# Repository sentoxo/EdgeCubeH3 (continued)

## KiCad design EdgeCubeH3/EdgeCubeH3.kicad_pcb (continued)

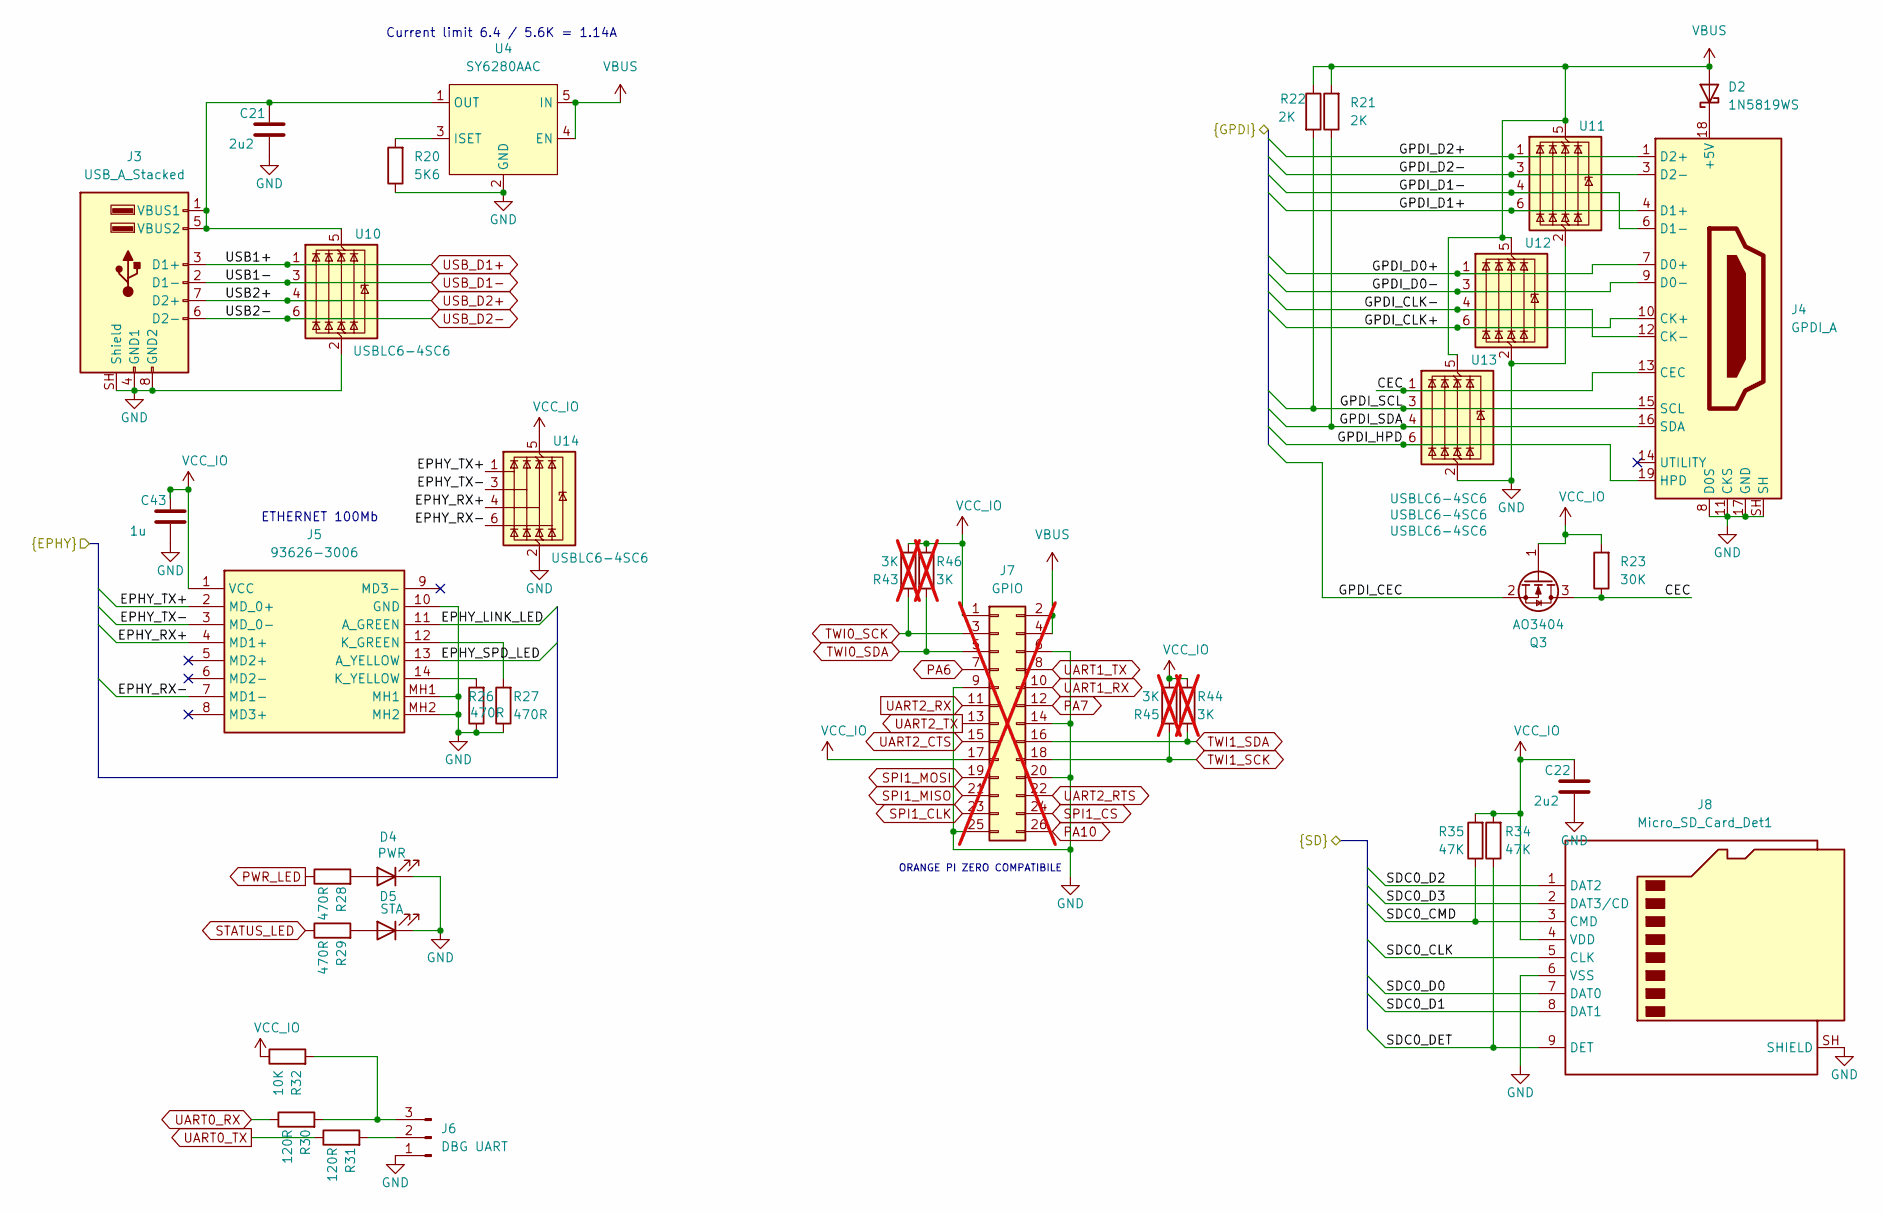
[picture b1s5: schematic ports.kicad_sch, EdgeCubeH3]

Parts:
C21, C22: 2u2; C_0603_1608Metric
C43: 1u; C_0603_1608Metric
D2: 1N5819WS; D_SOD-323
D4: PWR; LED_0805_2012Metric
D5: STA; LED_0805_2012Metric
J3: USB_A_Stacked; USB_A_CUI_UJ2-ADH-TH_Horizontal_Stacked
J4: GPDI_A; HDMI_A_Molex_208658-1001_Horizontal
J5: 93626-3006; 936263006; Mouser Part Number 538-93626-3006
J6: DBG UART; PinHeader_1x03_P2.54mm_Vertical
J7: GPIO; PinHeader_2x13_P2.54mm_Vertical; not fitted
J8: Micro_SD_Card_Det1; microSD_TF-01A
Q3: AO3404; SOT-23
R20: 5K6; R_0603_1608Metric
R21, R22: 2K; R_0603_1608Metric
R23: 30K; R_0603_1608Metric
R26, R27, R28, R29: 470R; R_0603_1608Metric
R30, R31: 120R; R_0603_1608Metric
R32: 10K; R_0603_1608Metric
R34, R35: 47K; R_0603_1608Metric
R43, R44, R45, R46: 3K; R_0603_1608Metric; not fitted
U4: SY6280AAC; SOT-23-5; LCSC Part # C55136
U10, U11, U12, U13, U14: USBLC6-4SC6; SOT-23-6

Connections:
/SoC/EPHY_LINK_LED: J5.11 (A_GREEN); also elsewhere on the board
/SoC/EPHY_RX+: J5.4 (MD1+), U14.4 (I/O3); also elsewhere on the board
/SoC/EPHY_RX-: J5.7 (MD1-), U14.6 (I/O4); also elsewhere on the board
/SoC/EPHY_SPD_LED: J5.13 (A_YELLOW); also elsewhere on the board
/SoC/EPHY_TX+: J5.2 (MD_0+), U14.1 (I/O1); also elsewhere on the board
/SoC/EPHY_TX-: J5.3 (MD_0-), U14.3 (I/O2); also elsewhere on the board
/SoC/GPDI_CEC: Q3.2 (S); also elsewhere on the board
/SoC/GPDI_CLK+: J4.10 (CK+), U12.6 (I/O4); also elsewhere on the board
/SoC/GPDI_CLK-: J4.12 (CK-), U12.4 (I/O3); also elsewhere on the board
/SoC/GPDI_D0+: J4.7 (D0+), U12.1 (I/O1); also elsewhere on the board
/SoC/GPDI_D0-: J4.9 (D0-), U12.3 (I/O2); also elsewhere on the board
/SoC/GPDI_D1+: J4.4 (D1+), U11.6 (I/O4); also elsewhere on the board
/SoC/GPDI_D1-: J4.6 (D1-), U11.4 (I/O3); also elsewhere on the board
/SoC/GPDI_D2+: J4.1 (D2+), U11.1 (I/O1); also elsewhere on the board
/SoC/GPDI_D2-: J4.3 (D2-), U11.3 (I/O2); also elsewhere on the board
/SoC/GPDI_HPD: J4.19 (HPD), U13.6 (I/O4); also elsewhere on the board
/SoC/GPDI_SCL: J4.15 (SCL), R22.2, U13.3 (I/O2); also elsewhere on the board
/SoC/GPDI_SDA: J4.16 (SDA), R21.1, U13.4 (I/O3); also elsewhere on the board
/SoC/SDC0_CLK: J8.5 (CLK); also elsewhere on the board
/SoC/SDC0_CMD: J8.3 (CMD), R35.1; also elsewhere on the board
/SoC/SDC0_D0: J8.7 (DAT0); also elsewhere on the board
/SoC/SDC0_D1: J8.8 (DAT1); also elsewhere on the board
/SoC/SDC0_D2: J8.1 (DAT2); also elsewhere on the board
/SoC/SDC0_D3: J8.2 (DAT3/CD); also elsewhere on the board
/SoC/SDC0_DET: J8.9 (DET), R34.1; also elsewhere on the board
/ports/CEC: J4.13 (CEC), Q3.3 (D), R23.1, U13.1 (I/O1)
GND: C21.2, C22.2, C43.2, D4.1 (K), D5.1 (K), J3.4 (GND1), J3.8 (GND2), J3.SH (Shield), J4.2 (D2S), J4.5 (D1S), J4.8 (D0S), J4.11 (CKS), J4.17 (GND), J4.SH, J5.10 (GND), J5.MH1, J5.MH2, J6.1, J7.6, J7.9, J7.14, J7.20, J7.25, J8.6 (VSS), J8.SH (SHIELD), R20.1, R26.1, R27.1, U4.2 (GND), U10.2 (GND), U11.2 (GND), U12.2 (GND), U13.2 (GND), U14.2 (GND); also elsewhere on the board
unnamed: D2.1 (K), J4.18 (+5V)
unnamed: D4.2 (A), R28.2
unnamed: D5.2 (A), R29.2
unnamed: C21.1, J3.1 (VBUS1), J3.5 (VBUS2), U4.1 (OUT), U10.5 (VBUS)
unnamed: J5.12 (K_GREEN), R27.2
unnamed: J5.14 (K_YELLOW), R26.2
unnamed: J6.2, R31.2
unnamed: J6.3, R30.2, R32.2
unnamed: R20.2, U4.3 (ISET)
PA6: J7.7; also elsewhere on the board
PA7: J7.12; also elsewhere on the board
PA10: J7.26; also elsewhere on the board
PWR_LED: R28.1; also elsewhere on the board
SPI1_CLK: J7.23; also elsewhere on the board
SPI1_CS: J7.24; also elsewhere on the board
SPI1_MISO: J7.21; also elsewhere on the board
SPI1_MOSI: J7.19; also elsewhere on the board
STATUS_LED: R29.1; also elsewhere on the board
TWI0_SCK: J7.3, R43.2; also elsewhere on the board
TWI0_SDA: J7.5, R46.1; also elsewhere on the board
TWI1_SCK: J7.18, R45.2; also elsewhere on the board
TWI1_SDA: J7.16, R44.1; also elsewhere on the board
UART0_RX: R30.1; also elsewhere on the board
UART0_TX: R31.1; also elsewhere on the board
UART1_RX: J7.10; also elsewhere on the board
UART1_TX: J7.8; also elsewhere on the board
UART2_CTS: J7.15; also elsewhere on the board
UART2_RTS: J7.22; also elsewhere on the board
UART2_RX: J7.11; also elsewhere on the board
UART2_TX: J7.13; also elsewhere on the board
USB_D1+: J3.3 (D1+), U10.1 (I/O1); also elsewhere on the board
USB_D1-: J3.2 (D1-), U10.3 (I/O2); also elsewhere on the board
USB_D2+: J3.7 (D2+), U10.4 (I/O3); also elsewhere on the board
USB_D2-: J3.6 (D2-), U10.6 (I/O4); also elsewhere on the board
VBUS: D2.2 (A), J7.2, J7.4, R21.2, R22.1, U4.4 (EN), U4.5 (IN), U11.5 (VBUS), U12.5 (VBUS), U13.5 (VBUS); also elsewhere on the board
VCC_IO: C22.1, C43.1, J5.1 (VCC), J7.1, J7.17, J8.4 (VDD), Q3.1 (G), R23.2, R32.1, R34.2, R35.2, R43.1, R44.2, R45.1, R46.2, U14.5 (VBUS); also elsewhere on the board

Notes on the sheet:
ETHERNET 100Mb
Current limit 6.4 / 5.6K = 1.14A
ORANGE PI ZERO COMPATIBILE

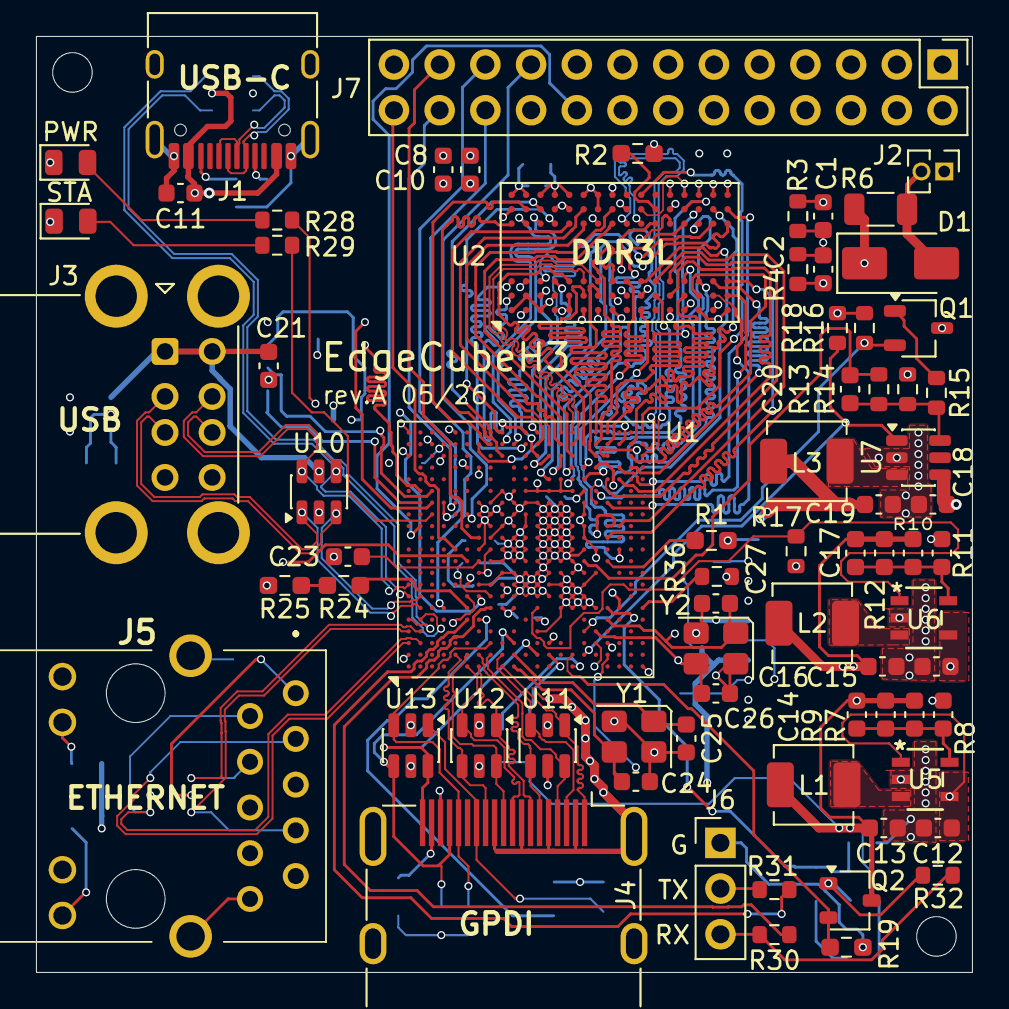
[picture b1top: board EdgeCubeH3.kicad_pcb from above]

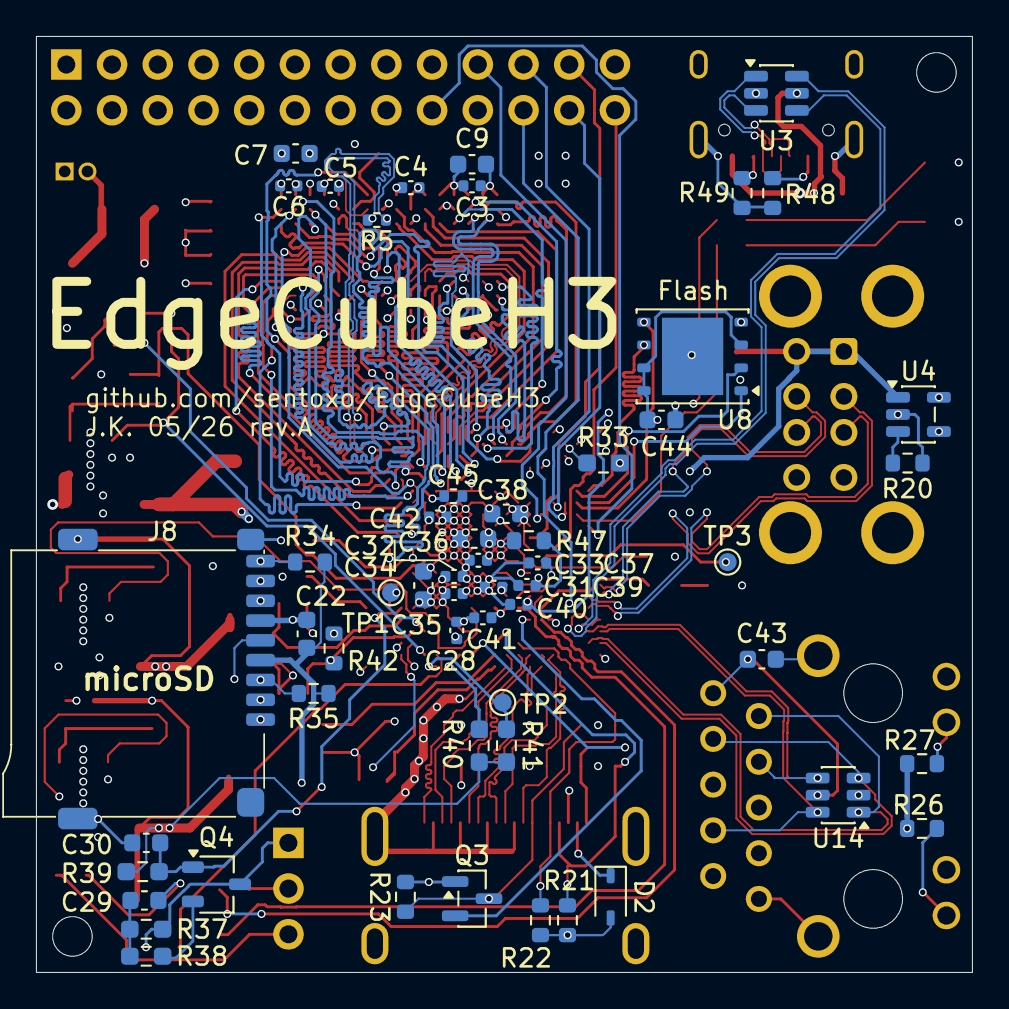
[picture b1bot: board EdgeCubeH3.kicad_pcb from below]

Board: 6 copper layers, 52.0 x 52.0 mm, 129 parts (55 on the bottom side), 159 nets.

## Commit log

2026-05-10 Schematic update, PCB started
2026-05-17 PCB design at ~90%
    - re-arrangement of components
    - connecting dram
    - connecting ports
2026-05-18 PCB at 95%
2026-05-19 PCB at 98%
2026-05-20 Compleating PCB design
2026-05-21 Small changes to PCB, updated schematic and readme
2026-05-23 Finalization of rev.A
